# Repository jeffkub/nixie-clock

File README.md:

# nixie-clock

An open source nixie clock with GPS time synchronization.

## Enclosure

The enclosure design has been moved to Fusion 360.  The files in the hardware folder are out of date and will be removed at some point.

1. [Enclosure](http://a360.co/2x962o5)
2. [PCB](http://a360.co/2x9v2f3)
3. [Assembly](http://a360.co/2y7SgBr)

## Build Instructions

The code was built on Ubuntu 16.04.  The [STM32Cube F3 library V1.9.0](http://www.st.com/content/st_com/en/products/embedded-software/mcus-embedded-software/stm32-embedded-software/stm32cube-embedded-software/stm32cubef3.html) will need to be installed to the `/opt/` directory.  The following apt packages are required.

```
cmake
gcc-arm-none-eabi
gdb-arm-none-eabi
```

To build the code.

```bash
mkdir firmware/nixie-clock/release
cd firmware/nixie-clock/release
cmake -DSTM32_CHIP=STM32F302C8 -DCMAKE_TOOLCHAIN_FILE=../../cmake/gcc_stm32.cmake -DSTM32Cube_DIR=/opt/STM32Cube_FW_F3_V1.9.0/ -DCMAKE_BUILD_TYPE=Release ..
make
```

To build for debugging.

```bash
mkdir firmware/nixie-clock/debug
cd firmware/nixie-clock/debug
cmake -DSTM32_CHIP=STM32F302C8 -DCMAKE_TOOLCHAIN_FILE=../../cmake/gcc_stm32.cmake -DSTM32Cube_DIR=/opt/STM32Cube_FW_F3_V1.9.0/ -DCMAKE_BUILD_TYPE=Debug ..
make
```

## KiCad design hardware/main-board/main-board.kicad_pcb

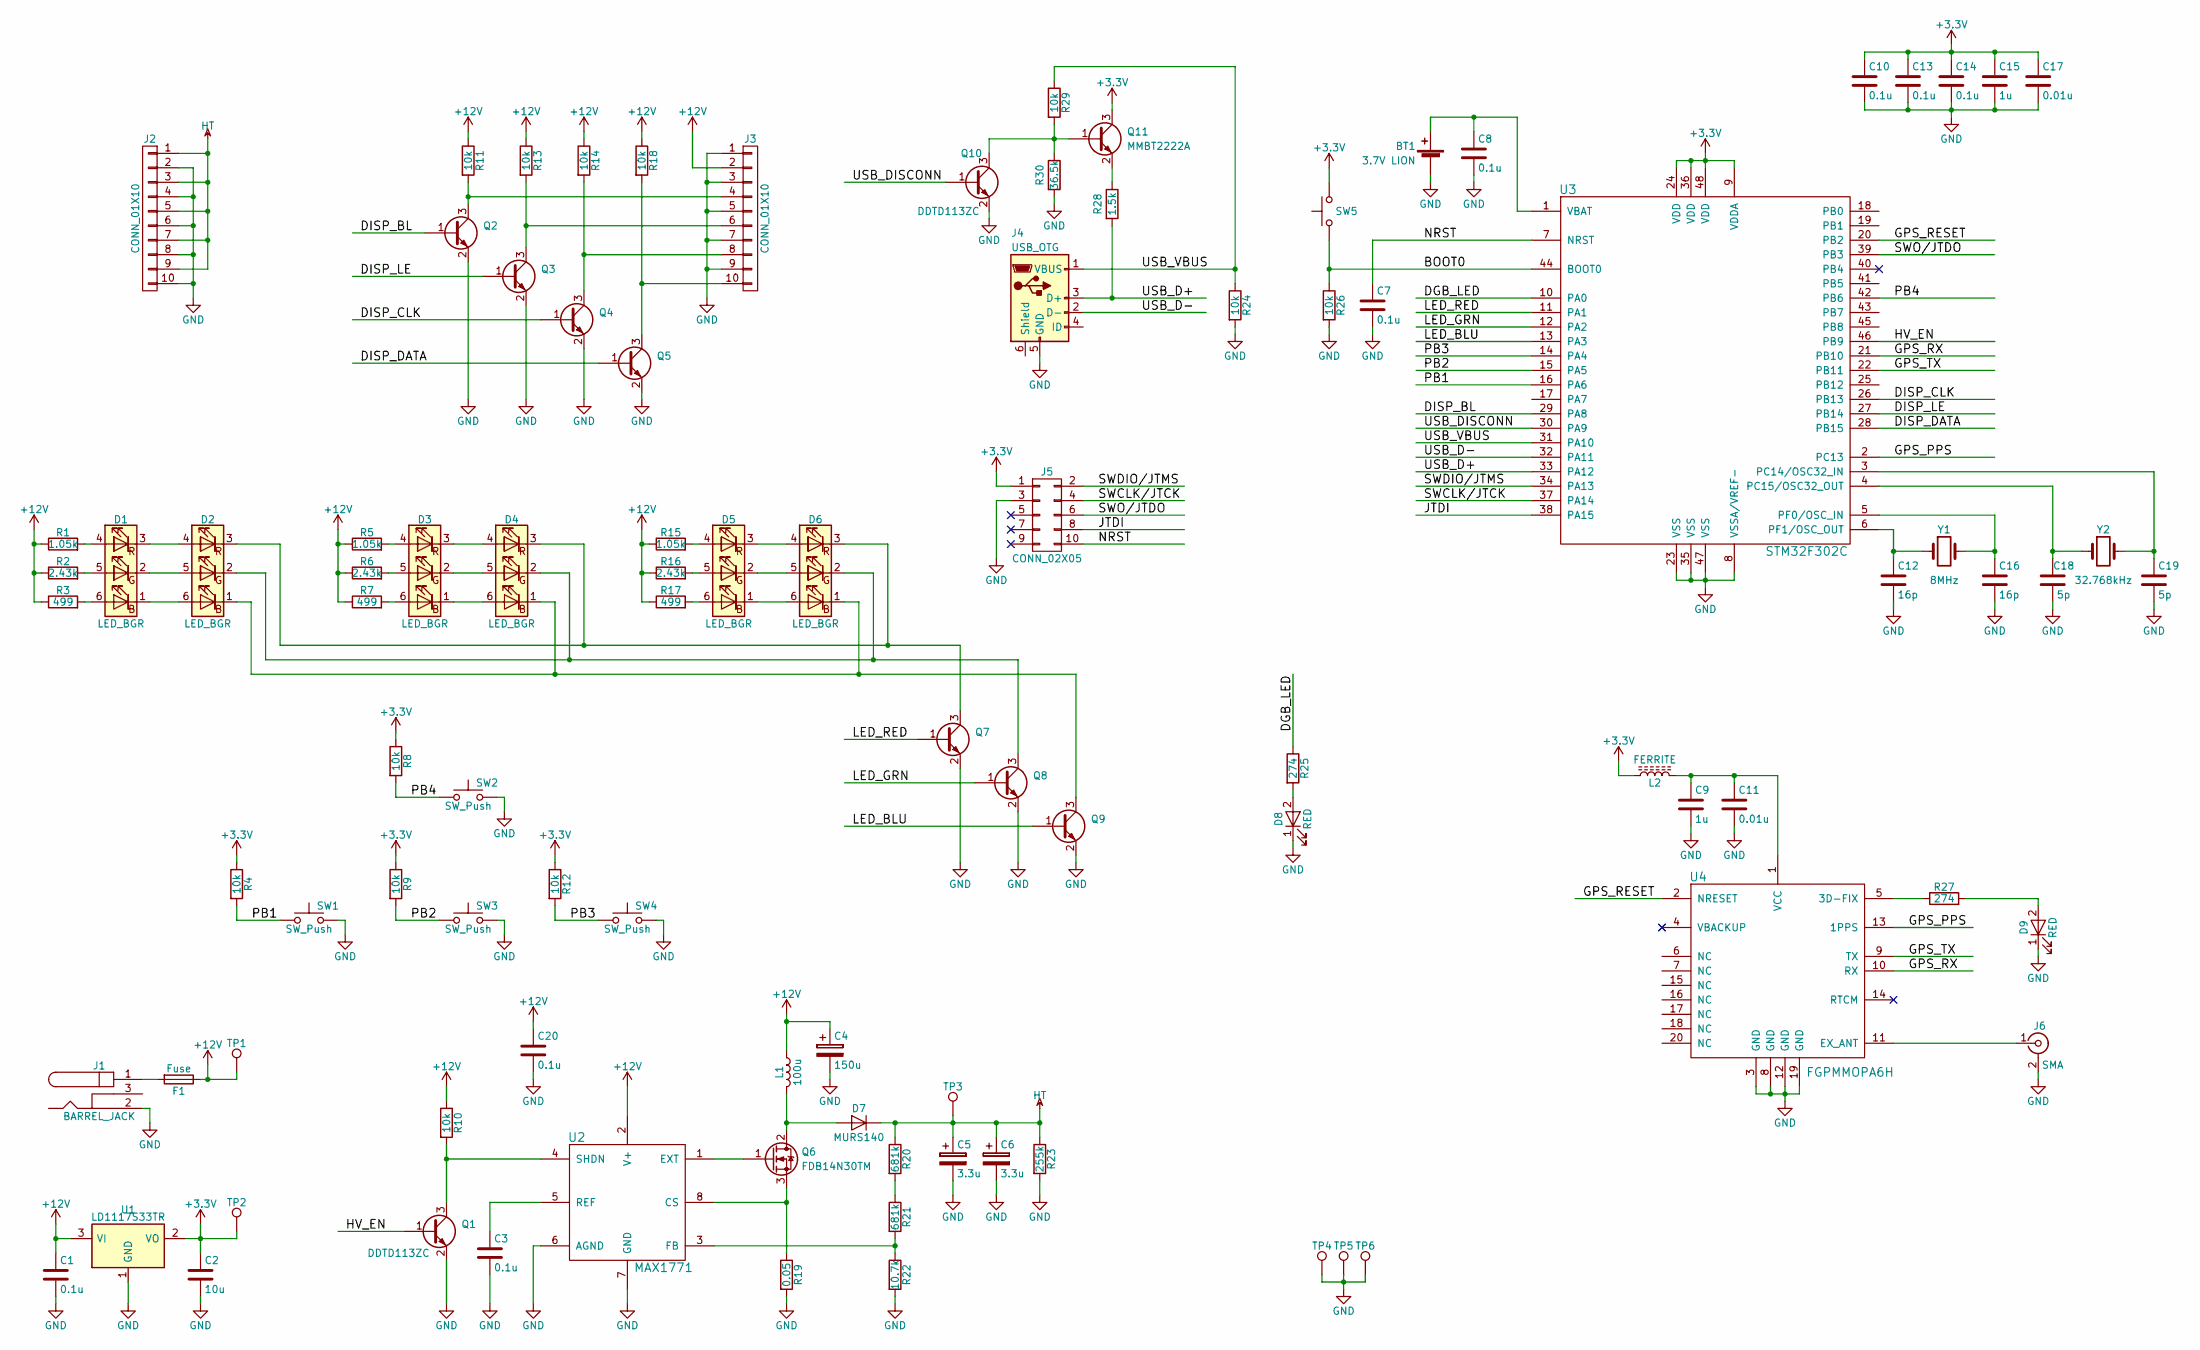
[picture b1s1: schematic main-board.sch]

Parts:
BT1: 3.7V LION; S8411-45R; Part 952-1745-1-ND
C1, C3, C7, C8, C10, C13, C14, C20: 0.1u; C_0603; Part 311-1344-1-ND
C2: 10u; C_0805; Part 311-1460-1-ND
C4: 150u; CP_Radial_D6.3mm_P2.50mm; Part P15352CT-ND
C5, C6: 3.3u; CP_Radial_D6.3mm_P2.50mm; Part 493-12639-1-ND
C9, C15: 1u; C_0805; Part 311-1365-1-ND
C11, C17: 0.01u; C_0603; Part 311-1085-1-ND
C12, C16: 16p; C_0603; Part 311-1751-1-ND
C18, C19: 5p; C_0603; Part 311-1054-1-ND
D1, D2, D3, D4, D5, D6: LED_BGR; PLCC-6; Part 516-3281-1-ND
D7: MURS140; D_SMB_Standard; Part MURS140-FDICT-ND
D8, D9: RED; D_1206; Part 160-1405-1-ND
F1: Fuse; 01110501Z; Part F4189-ND
J1: BARREL_JACK; PJ-002AH-SMT-TR; Part CP-002AHPJCT-ND
J2, J3: CONN_01X10; 8-188275-0; Part A99476CT-ND
J4: USB_OTG; 10118192; Part 609-4613-1-ND
J5: CONN_02X05; TC2050-IDC; Part NA
J6: SMA; SMA_THT_Jack_Straight; Part CONSMA002-L-ND
L1: 100u; DO3316P; Part 994-DO3316P-104MLD
L2: FERRITE; R_0805; Part 490-1054-1-ND
Q1, Q2, Q3, Q4, Q5, Q7, Q8, Q9, Q10: DDTD113ZC; SOT-23; Part DDTD113ZC-7FDICT-ND
Q6: FDB14N30TM; TO-263-2; Part FDB14N30TMCT-ND
Q11: MMBT2222A; SOT-23; Part MMBT2222A-FDICT-ND
R1, R5, R15: 1.05k; R_0805; Part 311-1.05KCRCT-ND
R2, R6, R16: 2.43k; R_0805; Part 311-2.43KCRCT-ND
R3, R7, R17: 499; R_0805; Part 311-499CRCT-ND
R4, R8, R9, R10, R11, R12, R13, R14, R18, R24, R26, R29: 10k; R_0805; Part 311-10.0KCRCT-ND
R19: 0.05; R_1206; Part 311-.05LWCT-ND
R20, R21: 681k; R_1206; Part 311-681KFRCT-ND
R22: 10.7k; R_1206; Part 311-10.7KFRCT-ND
R23: 255k; R_1206; Part 311-255KFRCT-ND
R25, R27: 274; R_0805; Part 311-274CRCT-ND
R28: 1.5k; R_0805; Part 311-1.50KCRCT-ND
R30: 36.5k; R_0805; Part 311-36.5KCRCT-ND
SW1, SW2, SW3, SW4: SW_Push; SW_PUSH_6mm; Part EG2505-ND
SW5: SW_Push; TL1105SF160Q; Part EG1839-ND
TP1, TP2, TP3, TP4, TP5, TP6: TP; Measurement_Point_Round-TH_Small; Part NA
U1: LD1117S33TR; SOT-223; Part 497-1242-1-ND
U2: MAX1771; SOIC-8_3.9x4.9mm_Pitch1.27mm; Part MAX1771CSA+CT-ND
U3: STM32F302C; LQFP-48_7x7mm_Pitch0.5mm; Part 497-14699-ND
U4: FGPMMOPA6H; Part 790
Y1: 8MHz; Crystal_SMD_HC49-SD; Part 535-10212-1-ND
Y2: 32.768kHz; ABS07; Part 535-9542-1-ND

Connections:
+3V3: C2.1, C10.1, C13.1, C14.1, C15.1, C17.1, J5.1, L2.1, Q11.3 (C), R4.1, R8.1, R9.1, R12.1, SW5.1, TP2.1, U1.2 (VO), U3.9 (VDDA), U3.24 (VDD), U3.36 (VDD), U3.48 (VDD)
+12V: C1.1, C4.1, C20.1, F1.1, J3.2, L1.1, R1.1, R2.1, R3.1, R5.1, R6.1, R7.1, R10.1, R11.1, R13.1, R14.1, R15.1, R16.1, R17.1, R18.1, TP1.1, U1.3 (VI), U2.2 (V+)
/BOOT0: R26.1, SW5.2, U3.44 (BOOT0)
/DGB_LED: R25.1, U3.10 (PA0)
/DISP_BL: Q2.1 (B), U3.29 (PA8)
/DISP_CLK: Q4.1 (B), U3.26 (PB13)
/DISP_DATA: Q5.1 (B), U3.28 (PB15)
/DISP_LE: Q3.1 (B), U3.27 (PB14)
/GPS_PPS: U3.2 (PC13), U4.13 (1PPS)
/GPS_RESET: U3.20 (PB2), U4.2 (NRESET)
/GPS_RX: U3.21 (PB10), U4.10 (RX)
/GPS_TX: U3.22 (PB11), U4.9 (TX)
/HV_EN: Q1.1 (B), U3.46 (PB9)
/JTDI: J5.8, U3.38 (PA15)
/LED_BLU: Q9.1 (B), U3.13 (PA3)
/LED_GRN: Q8.1 (B), U3.12 (PA2)
/LED_RED: Q7.1 (B), U3.11 (PA1)
/NRST: C7.1, J5.10, U3.7 (NRST)
/PB1: R4.2, SW1.1, U3.16 (PA6)
/PB2: R9.2, SW3.1, U3.15 (PA5)
/PB3: R12.2, SW4.1, U3.14 (PA4)
/PB4: R8.2, SW2.1, U3.42 (PB6)
/SWCLK/JTCK: J5.4, U3.37 (PA14)
/SWDIO/JTMS: J5.2, U3.34 (PA13)
/SWO/JTDO: J5.6, U3.39 (PB3)
/USB_D+: J4.3 (D+), R28.2, U3.33 (PA12)
/USB_D-: J4.2 (D-), U3.32 (PA11)
/USB_DISCONN: Q10.1 (B), U3.30 (PA9)
/USB_VBUS: J4.1 (VBUS), R24.1, R29.1, U3.31 (PA10)
GND: BT1.2 (-), C1.2, C2.2, C3.2, C4.2, C5.2, C6.2, C7.2, C8.2, C9.2, C10.2, C11.2, C12.2, C13.2, C14.2, C15.2, C16.2, C17.2, C18.2, C19.2, C20.2, D8.1 (K), D9.1 (K), J1.2, J2.2, J2.4, J2.6, J2.8, J2.10, J3.1, J3.3, J3.5, J3.7, J3.9, J4.5 (GND), J5.3, J6.2 (Ext), Q1.2 (E), Q2.2 (E), Q3.2 (E), Q4.2 (E), Q5.2 (E), Q7.2 (E), Q8.2 (E), Q9.2 (E), Q10.2 (E), R19.2, R22.2, R23.2, R24.2, R26.2, R30.2, SW1.2, SW2.2, SW3.2, SW4.2, TP4.1, TP5.1, TP6.1, U1.1 (GND), U2.6 (AGND), U2.7 (GND), U3.8 (VSSA/VREF-), U3.23 (VSS), U3.35 (VSS), U3.47 (VSS), U4.3 (GND), U4.8 (GND), U4.12 (GND), U4.19 (GND)
HT: C5.1, C6.1, D7.1 (K), J2.1, J2.3, J2.5, J2.7, J2.9, R20.1, R23.1, TP3.1
unnamed: BT1.1 (+), C8.1, U3.1 (VBAT)
unnamed: C3.1, U2.5 (REF)
unnamed: C9.1, C11.1, L2.2, U4.1 (VCC)
unnamed: C12.1, U3.6 (PF1/OSC_OUT), Y1.1
unnamed: C16.1, U3.5 (PF0/OSC_IN), Y1.2
unnamed: C18.1, U3.4 (PC15/OSC32_OUT), Y2.1
unnamed: C19.1, U3.3 (PC14/OSC32_IN), Y2.2
unnamed: D1.1 (BK), D2.6 (BA)
unnamed: D1.2 (GK), D2.5 (GA)
unnamed: D1.3 (RK), D2.4 (RA)
unnamed: D1.4 (RA), R1.2
unnamed: D1.5 (GA), R2.2
unnamed: D1.6 (BA), R3.2
unnamed: D2.1 (BK), D4.1 (BK), D6.1 (BK), Q9.3 (C)
unnamed: D2.2 (GK), D4.2 (GK), D6.2 (GK), Q8.3 (C)
unnamed: D2.3 (RK), D4.3 (RK), D6.3 (RK), Q7.3 (C)
unnamed: D3.1 (BK), D4.6 (BA)
unnamed: D3.2 (GK), D4.5 (GA)
unnamed: D3.3 (RK), D4.4 (RA)
unnamed: D3.4 (RA), R5.2
unnamed: D3.5 (GA), R6.2
unnamed: D3.6 (BA), R7.2
unnamed: D5.1 (BK), D6.6 (BA)
unnamed: D5.2 (GK), D6.5 (GA)
unnamed: D5.3 (RK), D6.4 (RA)
unnamed: D5.4 (RA), R15.2
unnamed: D5.5 (GA), R16.2
unnamed: D5.6 (BA), R17.2
unnamed: D7.2 (A), L1.2, Q6.2 (D)
unnamed: D8.2 (A), R25.2
unnamed: D9.2 (A), R27.2
unnamed: F1.2, J1.1
unnamed: J3.4, Q2.3 (C), R11.2
unnamed: J3.6, Q3.3 (C), R13.2
unnamed: J3.8, Q4.3 (C), R14.2
unnamed: J3.10, Q5.3 (C), R18.2
unnamed: J6.1 (In), U4.11 (EX_ANT)
unnamed: Q1.3 (C), R10.2, U2.4 (SHDN)
unnamed: Q6.1 (G), U2.1 (EXT)
unnamed: Q6.3 (S), R19.1, U2.8 (CS)
unnamed: Q10.3 (C), Q11.1 (B), R29.2, R30.1
unnamed: Q11.2 (E), R28.1
unnamed: R20.2, R21.1
unnamed: R21.2, R22.1, U2.3 (FB)
unnamed: R27.1, U4.5 (3D-FIX)

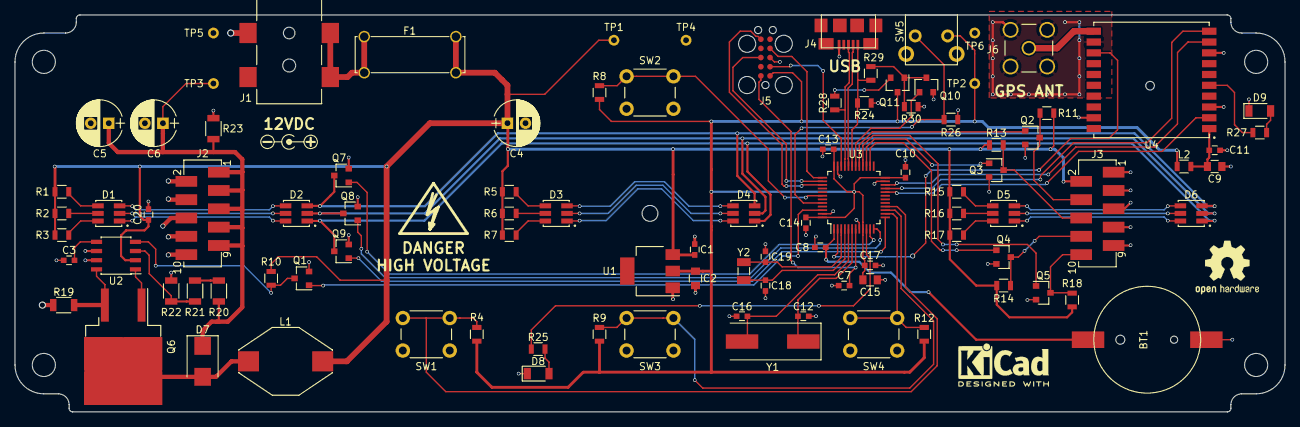
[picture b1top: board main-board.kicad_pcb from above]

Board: 2 copper layers, 176.0 x 55.0 mm, 97 parts (0 on the bottom side), 76 nets.

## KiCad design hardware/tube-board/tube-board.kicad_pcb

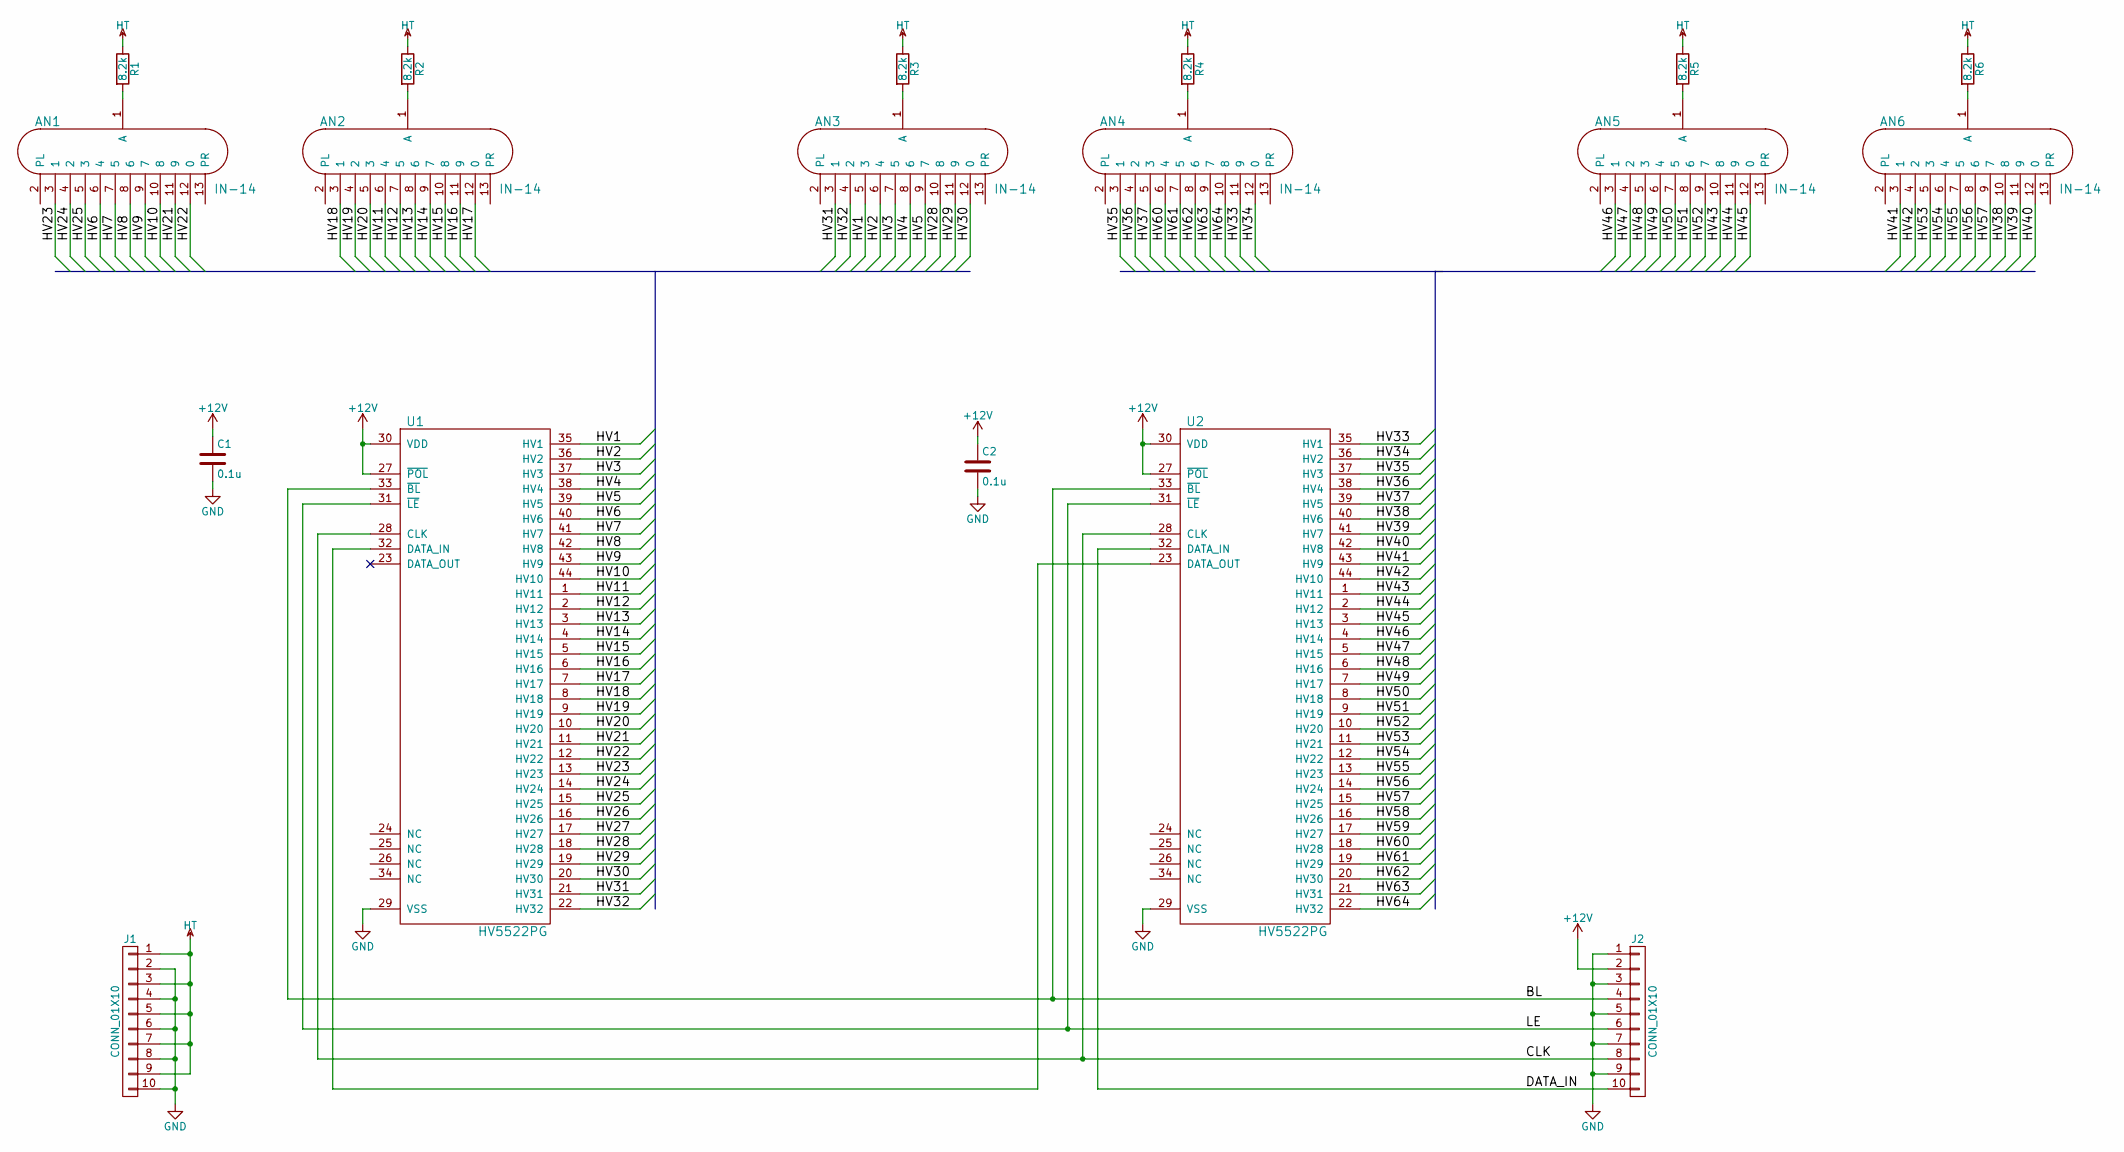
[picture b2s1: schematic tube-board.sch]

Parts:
AN1, AN2, AN3, AN4, AN5, AN6: IN-14
C1, C2: 0.1u; C_0603; Part 311-1344-1-ND
J1, J2: CONN_01X10; 1-338728-0; Part A116183CT-ND
R1, R2, R3, R4, R5, R6: 8.2k; R_1206; Part 311-8.20KFRCT-ND
U1, U2: HV5522PG; LQFP-44_10x10mm_Pitch0.8mm; Part 689-HV5522PG-G

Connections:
+12V: C1.1, C2.1, J2.2, U1.27 (~POL), U1.30 (VDD), U2.27 (~POL), U2.30 (VDD)
/BL: J2.4, U1.33 (~BL), U2.33 (~BL)
/CLK: J2.8, U1.28 (CLK), U2.28 (CLK)
/DATA_IN: J2.10, U2.32 (DATA_IN)
/HV1: AN3.5 (3), U1.35 (HV1)
/HV2: AN3.6 (4), U1.36 (HV2)
/HV3: AN3.7 (5), U1.37 (HV3)
/HV4: AN3.8 (6), U1.38 (HV4)
/HV5: AN3.9 (7), U1.39 (HV5)
/HV6: AN1.6 (4), U1.40 (HV6)
/HV7: AN1.7 (5), U1.41 (HV7)
/HV8: AN1.8 (6), U1.42 (HV8)
/HV9: AN1.9 (7), U1.43 (HV9)
/HV10: AN1.10 (8), U1.44 (HV10)
/HV11: AN2.6 (4), U1.1 (HV11)
/HV12: AN2.7 (5), U1.2 (HV12)
/HV13: AN2.8 (6), U1.3 (HV13)
/HV14: AN2.9 (7), U1.4 (HV14)
/HV15: AN2.10 (8), U1.5 (HV15)
/HV16: AN2.11 (9), U1.6 (HV16)
/HV17: AN2.12 (0), U1.7 (HV17)
/HV18: AN2.3 (1), U1.8 (HV18)
/HV19: AN2.4 (2), U1.9 (HV19)
/HV20: AN2.5 (3), U1.10 (HV20)
/HV21: AN1.11 (9), U1.11 (HV21)
/HV22: AN1.12 (0), U1.12 (HV22)
/HV23: AN1.3 (1), U1.13 (HV23)
/HV24: AN1.4 (2), U1.14 (HV24)
/HV25: AN1.5 (3), U1.15 (HV25)
/HV26: U1.16 (HV26)
/HV27: U1.17 (HV27)
/HV28: AN3.10 (8), U1.18 (HV28)
/HV29: AN3.11 (9), U1.19 (HV29)
/HV30: AN3.12 (0), U1.20 (HV30)
/HV31: AN3.3 (1), U1.21 (HV31)
/HV32: AN3.4 (2), U1.22 (HV32)
/HV33: AN4.11 (9), U2.35 (HV1)
/HV34: AN4.12 (0), U2.36 (HV2)
/HV35: AN4.3 (1), U2.37 (HV3)
/HV36: AN4.4 (2), U2.38 (HV4)
/HV37: AN4.5 (3), U2.39 (HV5)
/HV38: AN6.10 (8), U2.40 (HV6)
/HV39: AN6.11 (9), U2.41 (HV7)
/HV40: AN6.12 (0), U2.42 (HV8)
/HV41: AN6.3 (1), U2.43 (HV9)
/HV42: AN6.4 (2), U2.44 (HV10)
/HV43: AN5.10 (8), U2.1 (HV11)
/HV44: AN5.11 (9), U2.2 (HV12)
/HV45: AN5.12 (0), U2.3 (HV13)
/HV46: AN5.3 (1), U2.4 (HV14)
/HV47: AN5.4 (2), U2.5 (HV15)
/HV48: AN5.5 (3), U2.6 (HV16)
/HV49: AN5.6 (4), U2.7 (HV17)
/HV50: AN5.7 (5), U2.8 (HV18)
/HV51: AN5.8 (6), U2.9 (HV19)
/HV52: AN5.9 (7), U2.10 (HV20)
/HV53: AN6.5 (3), U2.11 (HV21)
/HV54: AN6.6 (4), U2.12 (HV22)
/HV55: AN6.7 (5), U2.13 (HV23)
/HV56: AN6.8 (6), U2.14 (HV24)
/HV57: AN6.9 (7), U2.15 (HV25)
/HV58: U2.16 (HV26)
/HV59: U2.17 (HV27)
/HV60: AN4.6 (4), U2.18 (HV28)
/HV61: AN4.7 (5), U2.19 (HV29)
/HV62: AN4.8 (6), U2.20 (HV30)
/HV63: AN4.9 (7), U2.21 (HV31)
/HV64: AN4.10 (8), U2.22 (HV32)
/LE: J2.6, U1.31 (~LE), U2.31 (~LE)
GND: C1.2, C2.2, J1.2, J1.4, J1.6, J1.8, J1.10, J2.1, J2.3, J2.5, J2.7, J2.9, U1.29 (VSS), U2.29 (VSS)
HT: J1.1, J1.3, J1.5, J1.7, J1.9, R1.1, R2.1, R3.1, R4.1, R5.1, R6.1
unnamed: AN1.1 (A), R1.2
unnamed: AN2.1 (A), R2.2
unnamed: AN3.1 (A), R3.2
unnamed: AN4.1 (A), R4.2
unnamed: AN5.1 (A), R5.2
unnamed: AN6.1 (A), R6.2
unnamed: U1.32 (DATA_IN), U2.23 (DATA_OUT)

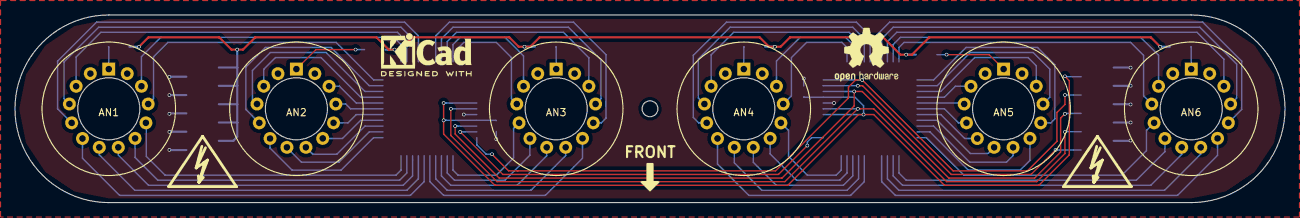
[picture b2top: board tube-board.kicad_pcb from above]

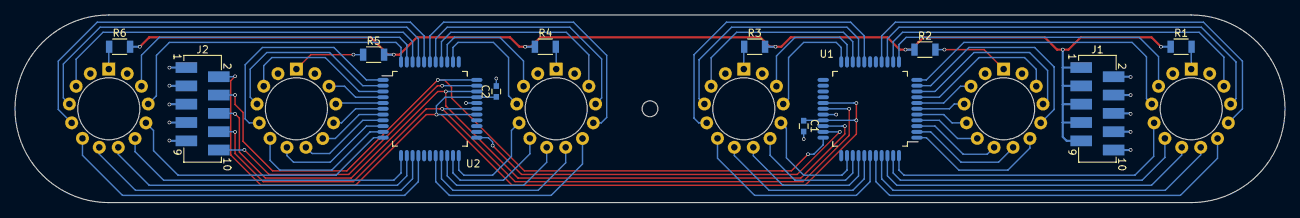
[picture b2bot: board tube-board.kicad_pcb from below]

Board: 2 copper layers, 176.0 x 26.0 mm, 18 parts (12 on the bottom side), 74 nets.

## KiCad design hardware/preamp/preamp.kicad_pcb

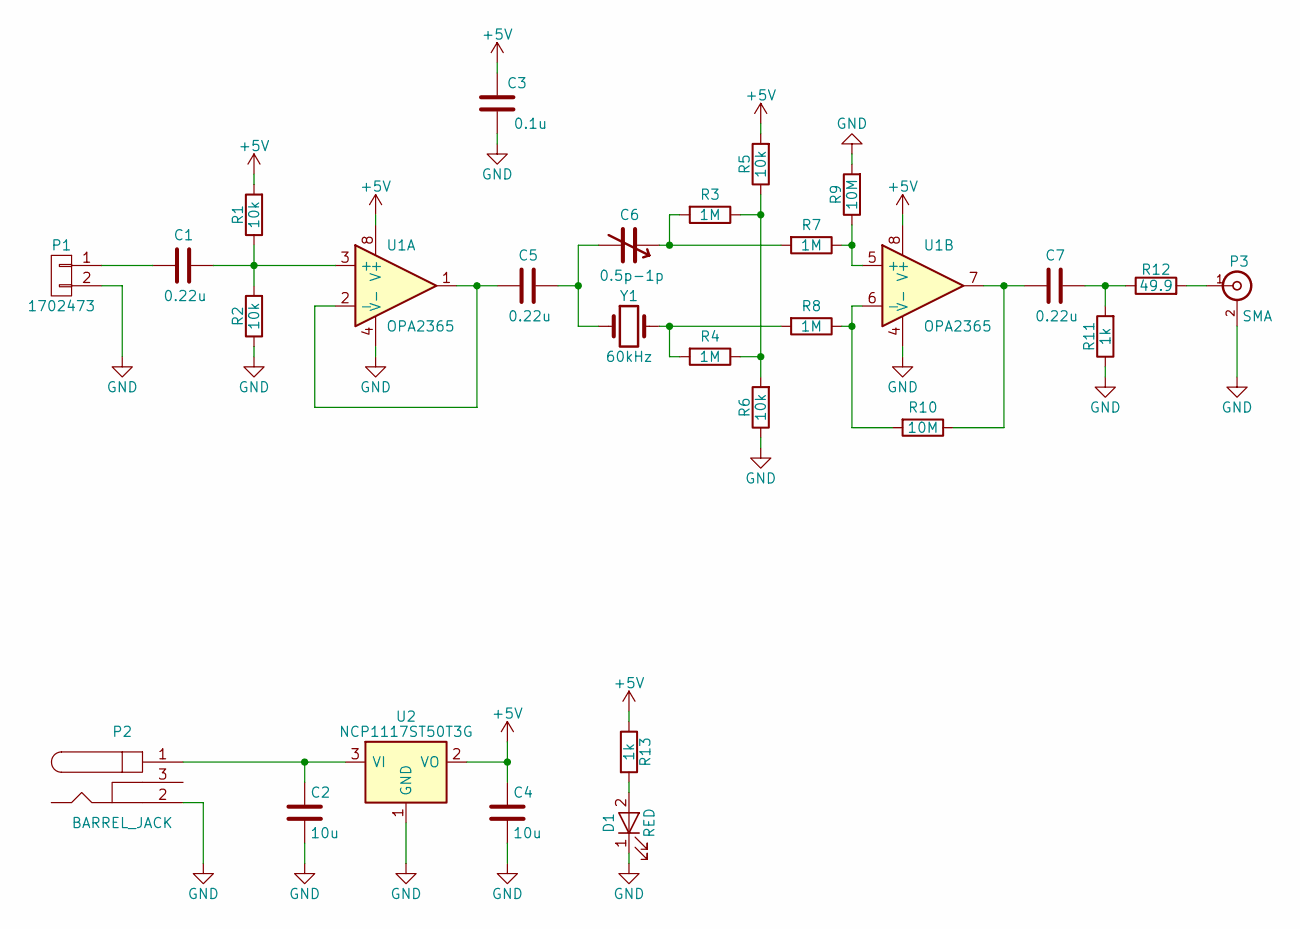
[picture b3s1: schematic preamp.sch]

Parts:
C1, C5, C7: 0.22u; C_0603; Part 311-1426-1-ND
C2, C4: 10u; C_0805; Part 311-1460-1-ND
C3: 0.1u; C_0603; Part 311-1344-1-ND
C6: 0.5p-1p; TZY2; Part 490-12520-ND
D1: RED; D_0603; Part 160-1447-1-ND
P1: 1702473; Part 277-2337-1-ND
P2: BARREL_JACK; PJ-002AH-SMT-TR; Part CP-002AHPJCT-ND
P3: SMA; 142-0701-801; Part J502-ND
R1, R2, R5, R6: 10k; R_0603; Part 311-10.0KHRCT-ND
R3, R4, R7, R8: 1M; R_0603; Part 311-1.00MHRCT-ND
R9, R10: 10M; R_0603; Part 311-10.0MHRCT-ND
R11, R13: 1k; R_0603; Part 311-1.00KHRCT-ND
R12: 49.9; R_0603; Part 311-49.9HRCT-ND
U1: OPA2365; SOIC-8_3.9x4.9mm_Pitch1.27mm; Part 296-31704-1-ND
U2: NCP1117ST50T3G; SOT-223; Part NCP1117ST50T3GOSCT-ND
Y1: 60kHz; Crystal_DS26_d2.0mm_l6.0mm_Horizontal_1EP_style1; Part SER3320-ND

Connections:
+5V: C3.2, C4.1, R1.2, R5.2, R13.1, U1.8 (V+), U2.2 (VO)
GND: C2.2, C3.1, C4.2, D1.1 (K), P1.2, P2.2, P3.2 (Ext), R2.1, R6.1, R9.2, R11.1, U1.4 (V-), U2.1 (GND)
unnamed: C1.1, R1.1, R2.2, U1.3 (+)
unnamed: C1.2, P1.1
unnamed: C2.1, P2.1, U2.3 (VI)
unnamed: C5.1, C6.2, Y1.1
unnamed: C5.2, U1.1, U1.2 (-)
unnamed: C6.1, R3.2, R7.2
unnamed: C7.1, R11.2, R12.1
unnamed: C7.2, R10.1, U1.7
unnamed: D1.2 (A), R13.2
unnamed: P3.1 (In), R12.2
unnamed: R3.1, R4.1, R5.1, R6.2
unnamed: R4.2, R8.2, Y1.2
unnamed: R7.1, R9.1, U1.5 (+)
unnamed: R8.1, R10.2, U1.6 (-)

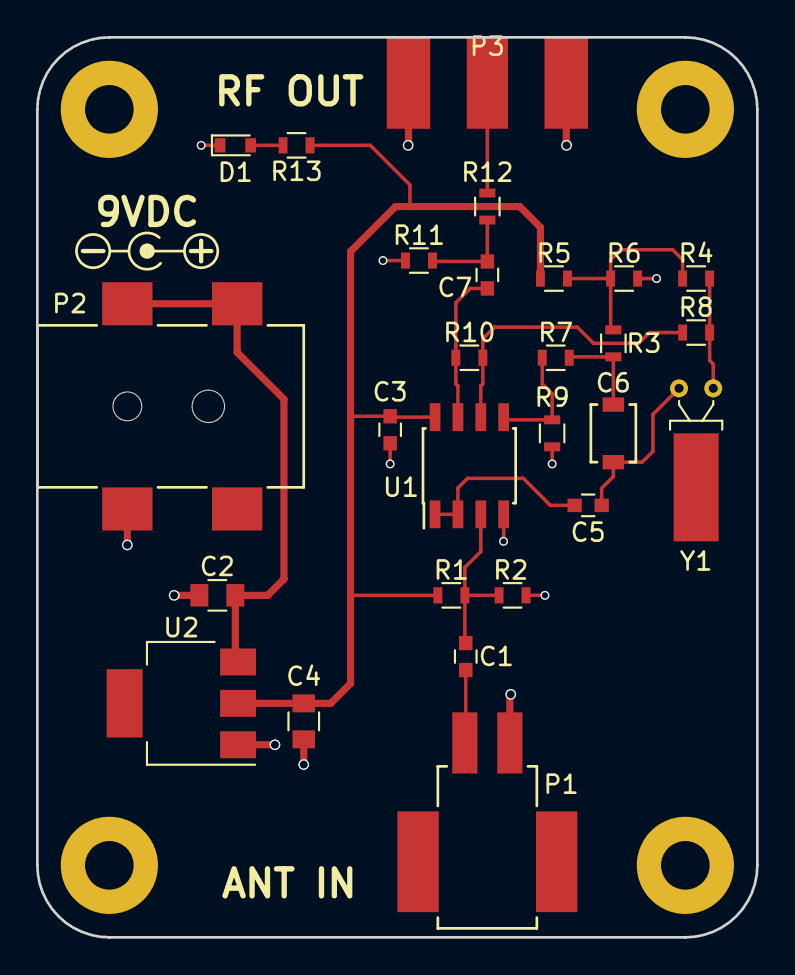
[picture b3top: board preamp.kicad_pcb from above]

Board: 2 copper layers, 40.0 x 50.0 mm, 27 parts (0 on the bottom side), 16 nets.

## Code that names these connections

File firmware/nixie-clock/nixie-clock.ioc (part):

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Mcu.Name=STM32F302C(6-8)Tx
Mcu.Package=LQFP48
Mcu.UserName=STM32F302C8Tx
PA0.Signal=S_TIM2_CH1_ETR
PA1.Signal=S_TIM2_CH2
PA10.GPIOParameters=GPIO_Label
PA10.GPIO_Label=USB_VBUS
PA10.Signal=GPIO_Input
PA11.Mode=Device
PA11.Signal=USB_DM
PA12.Mode=Device
PA12.Signal=USB_DP
PA13.Mode=JTAG_4_pins
PA13.Signal=SYS_JTMS-SWDIO
PA14.Mode=JTAG_4_pins
PA14.Signal=SYS_JTCK-SWCLK
PA15.Mode=JTAG_4_pins
PA15.Signal=SYS_JTDI
PA2.Signal=S_TIM2_CH3
PA3.Signal=S_TIM2_CH4
PA4.GPIOParameters=GPIO_Label
PA4.GPIO_Label=PB3
PA4.Signal=GPIO_Input
PA5.GPIOParameters=GPIO_Label
PA5.GPIO_Label=PB2
PA5.Signal=GPIO_Input
PA6.GPIOParameters=GPIO_Label
PA6.GPIO_Label=PB1
PA6.Signal=GPIO_Input
PA8.GPIOParameters=PinState,GPIO_Label
PA8.GPIO_Label=DISP_BL
PA8.PinState=GPIO_PIN_SET
PA8.Signal=GPIO_Output
PB10.Mode=Asynchronous
PB10.Signal=USART3_TX
PB11.Mode=Asynchronous
PB11.Signal=USART3_RX
PB13.Mode=TX_Only_Simplex_Unidirect_Master
PB13.Signal=SPI2_SCK
PB14.GPIOParameters=GPIO_Label
PB14.GPIO_Label=DISP_LE
PB14.Signal=GPIO_Output
PB15.Mode=TX_Only_Simplex_Unidirect_Master
PB15.Signal=SPI2_MOSI
PB2.GPIOParameters=GPIO_Label
PB2.GPIO_Label=GPS_RESET
PB2.Signal=GPIO_Output
PB3.Mode=JTAG_4_pins
PB3.Signal=SYS_JTDO-TRACESWO
PB6.GPIOParameters=GPIO_Label
PB6.GPIO_Label=PB4
PB6.Signal=GPIO_Input
PB9.GPIOParameters=GPIO_Label
PB9.GPIO_Label=HV_EN
PB9.Signal=GPIO_Output
PC13.Mode=Timestamp enabled
PC13.Signal=RTC_TS
PC14\ -\ OSC32_IN.Mode=LSE-External-Oscillator
PC14\ -\ OSC32_IN.Signal=RCC_OSC32_IN
PC15\ -\ OSC32_OUT.Mode=LSE-External-Oscillator
PC15\ -\ OSC32_OUT.Signal=RCC_OSC32_OUT
PF0-OSC_IN.Mode=HSE-External-Oscillator
PF0-OSC_IN.Signal=RCC_OSC_IN
PF1-OSC_OUT.Mode=HSE-External-Oscillator
PF1-OSC_OUT.Signal=RCC_OSC_OUT
RCC.HSEPLLFreq_Value=8000000
RCC.HSE_VALUE=8000000
RCC.SYSCLKFreq_VALUE=72000000
RCC.SYSCLKSourceVirtual=RCC_SYSCLKSOURCE_PLLCLK
board=nixie-clock

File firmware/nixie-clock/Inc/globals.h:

/*******************************************************************************
MIT License

Copyright (c) 2017 Jeff Kubascik

Permission is hereby granted, free of charge, to any person obtaining a copy
of this software and associated documentation files (the "Software"), to deal
in the Software without restriction, including without limitation the rights
to use, copy, modify, merge, publish, distribute, sublicense, and/or sell
copies of the Software, and to permit persons to whom the Software is
furnished to do so, subject to the following conditions:

The above copyright notice and this permission notice shall be included in all
copies or substantial portions of the Software.

THE SOFTWARE IS PROVIDED "AS IS", WITHOUT WARRANTY OF ANY KIND, EXPRESS OR
IMPLIED, INCLUDING BUT NOT LIMITED TO THE WARRANTIES OF MERCHANTABILITY,
FITNESS FOR A PARTICULAR PURPOSE AND NONINFRINGEMENT. IN NO EVENT SHALL THE
AUTHORS OR COPYRIGHT HOLDERS BE LIABLE FOR ANY CLAIM, DAMAGES OR OTHER
LIABILITY, WHETHER IN AN ACTION OF CONTRACT, TORT OR OTHERWISE, ARISING FROM,
OUT OF OR IN CONNECTION WITH THE SOFTWARE OR THE USE OR OTHER DEALINGS IN THE
SOFTWARE.
*******************************************************************************/

#ifndef __GLOBALS_H
#define __GLOBALS_H

/* Includes *******************************************************************/
#include <ctype.h>
#include <stdbool.h>
#include <stdio.h>
#include <stdlib.h>
#include <string.h>
#include <time.h>

#include <sys/types.h>


/* Definitions ****************************************************************/

/* GPIO pin definitions */
#define DBG_LED_Pin             GPIO_PIN_0
#define DBG_LED_GPIO_Port       GPIOA

#define LED_RED_Pin             GPIO_PIN_1
#define LED_RED_GPIO_Port       GPIOA

#define LED_GRN_Pin             GPIO_PIN_2
#define LED_GRN_GPIO_Port       GPIOA

#define LED_BLU_Pin             GPIO_PIN_3
#define LED_BLU_GPIO_Port       GPIOA

#define PB1_Pin                 GPIO_PIN_6
#define PB1_GPIO_Port           GPIOA

#define PB2_Pin                 GPIO_PIN_5
#define PB2_GPIO_Port           GPIOA

#define PB3_Pin                 GPIO_PIN_4
#define PB3_GPIO_Port           GPIOA

#define PB4_Pin                 GPIO_PIN_6
#define PB4_GPIO_Port           GPIOB

#define GPS_RESET_Pin           GPIO_PIN_2
#define GPS_RESET_GPIO_Port     GPIOB

#define GPS_PPS_Pin             GPIO_PIN_13
#define GPS_PPS_GPIO_Port       GPIOC

#define GPS_RX_Pin              GPIO_PIN_10
#define GPS_RX_GPIO_Port        GPIOB

#define GPS_TX_Pin              GPIO_PIN_11
#define GPS_TX_GPIO_Port        GPIOB

#define DISP_LE_Pin             GPIO_PIN_14
#define DISP_LE_GPIO_Port       GPIOB

#define DISP_BL_Pin             GPIO_PIN_8
#define DISP_BL_GPIO_Port       GPIOA

#define DISP_CLK_Pin            GPIO_PIN_13
#define DISP_CLK_GPIO_Port      GPIOB

#define DISP_DATA_Pin           GPIO_PIN_15
#define DISP_DATA_GPIO_Port     GPIOB

#define USB_VBUS_Pin            GPIO_PIN_10
#define USB_VBUS_GPIO_Port      GPIOA

#define HV_EN_Pin               GPIO_PIN_9
#define HV_EN_GPIO_Port         GPIOB

/* Interrupt priorities - smaller number is higher priority.  Priorities must be
 * lower (larger) than configLIBRARY_MAX_SYSCALL_INTERRUPT_PRIORITY. */
#define EXTI15_10_IRQ_PRIORITY           5
#define SPI2_IRQ_PRIORITY                8
#define USART3_IRQ_PRIORITY              8
#define USB_LP_CAN_RX0_IRQ_PRIORITY      8
#define TIM2_IRQ_PRIORITY               10
#define RTC_WKUP_IRQ_PRIORITY           10
#define SYSTICK_IRQ_PRIORITY            15

/* Task priorities - larger number is higher priority. */
#define LED_TASK_PRIORITY                3
#define GPS_TASK_PRIORITY                2
#define MAIN_TASK_PRIORITY               1

#endif /* __GLOBALS_H */

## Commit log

2017-04-01 Adding preamp board
2017-04-01 Created schematic PDF
2017-04-01 Moved footprint library into hardware folder
2017-04-01 Working on clock schematic
2017-04-02 Working on schematic
2017-04-02 Split design into two boards
2017-04-02 Working on tube board schematic
2017-04-02 Completed tube board schematic
2017-04-02 Working on footprints
2017-04-03 Working on tube board layout
2017-04-05 Working on main board schematic
2017-04-05 Modified HV5522 footprint to have oval pads
2017-04-06 Finished tube board
2017-04-09 Working on main board layout
2017-04-13 Added bypass cap to MAX1771. Cleaning up PCB design
2017-04-14 Using DIP switch for BOOT mode. Minor layout changes
2017-04-14 Final tweaks before board submission
2017-04-14 Completed BOMs for both boards
2017-04-14 Working on 3D models for main board
2017-04-14 Fixed BOM part number error on tube-board
2017-04-17 Working on enclosure
2017-04-19 Working on lazer cutter drawings
2017-04-20 Changing acrylic thickness to match what is available
2017-04-25 Created laser cutter drawing
2017-04-28 Created laser cut svg drawings
2017-05-02 Added rubber feet to assembly
2017-05-08 Removed preamp board. Created firmware project
2017-05-09 Debug and RGB LED PWM now working
2017-05-10 Fixed HV5522 footprint on tube board. Increased size of IN-14 through holes. Fixed footprint for MOSFET in HV boost circuit. Fixed hole size for battery holder footprint.
2017-05-10 Switched to an 0603 capacitor on tube board
2017-05-11 Modified thermal relief on SMA connector
2017-05-11 Enabled semihosting for printf debugging
2017-05-23 Working on nixie driver module
2017-05-30 Working on display driver module
2017-06-10 Test code for nixie tubes working
2017-06-15 Updated current limit resistors for nixie tubes
2017-06-16 Working on GPS interface module
2017-06-18 Cleaning up nixie driver module
2017-06-18 Added labels to GPIO pins
2017-06-18 Working on gps module
2017-06-21 Added error handler for UART
2017-06-21 Added read line function
2017-07-05 Working on custom uart driver module
2017-07-06 Working on uart driver
2017-07-07 Now using custom uart driver for reading from gps
2017-07-15 Moved read line function into uart module
2017-07-15 Able to build application with cmake
2017-07-15 Added usb layers to build. Removed libraries from build (now compiling as a single binary)
2017-07-16 Code running on target
2017-07-16 Removed unused file
2017-07-17 Able to parse gps time string
2017-07-17 Working on GPS sentence parsing
2017-07-18 Successfully parsing UTC time and Date fields from GPS sentence
2017-07-18 Working on rtc driver module
2017-07-18 Working on rtc driver
2017-07-19 Working on rtWorking on rtc driver
2017-07-19 RTC wakeup interrupt now working
2017-07-20 Added function to read RTC time
2017-07-21 Enabled LSE oscillator for RTC clock
2017-07-21 Minor change to display task
2017-07-22 Working on RTC timestamp for GPS clock sync
2017-07-22 Added function to adjust RTC by subsecond amount
2017-07-23 Working on RTC GPS time sync
2017-07-26 Added semihosting for printf debugging
2017-07-27 Working on gps time sync
2017-07-28 Working on timezone module
2017-07-30 Minor code cleanup
2017-07-30 Now displaying local time
2017-08-04 Modified timezone definition to specify dst/std hour in local time
2017-08-04 Major code cleanup
2017-08-04 Fixed build error for release build
2017-08-19 Created debug_printf macro
2017-08-20 Modified RTC driver to bypass shadow registers
2017-08-20 Added ISR safe function to get RTC time
2017-08-20 Added IRQ handler for GPS pps signal that reads the RTC time
2017-08-21 Using queue to pass timestamp value to gps thread
2017-08-22 Created #defines for IRQ priorities
2017-08-23 Working on sub-second time adjustment
2017-08-24 Cleaned up gps module. Now making subsec adjustments to sync RTC to GPS
2017-08-24 Created PWM module to replace the STM32 HAL timer library
2017-08-24 No longer need floating point support in gps task
2017-08-24 Removed cmsis os files and using native FreeRTOS APIs
2017-08-24 Created spi driver module
2017-08-24 Moving gpio config
2017-08-25 Working on SPI driver module
2017-08-27 SPI driver module working
2017-08-27 Cleaning up driver code
2017-08-27 Added function to wait for PWM timer to reload
2017-08-27 Code cleanup
2017-08-27 Cleaning up code
2017-08-27 Working on RGB LED pattern
2017-08-27 Putting CPU to sleep when FreeRTOS is idle
2017-08-28 Tweaking pwm timer clock
2017-08-28 Working on color module. Cleaned up compiler warnings
2017-08-28 Now cycling hues with the RGB LEDs
2017-08-29 Reorganized source files
2017-08-29 Removed unused files
2017-08-30 Switched FreeRTOS heap to use stdlib
2017-08-31 Squaring LED brightness value to adjust for perceived intensity
2017-08-31 Updated USB library
2017-08-31 Fixed USB driver build errors
2017-08-31 Working on USB driver
2017-09-04 Added pull up circuit for USB. Changed boot switch to a right angle pushbutton so that it can be used to switch to bootloader mode within the enclosure
2017-09-17 Added 3d render picture
2017-09-17 Cropped picture
